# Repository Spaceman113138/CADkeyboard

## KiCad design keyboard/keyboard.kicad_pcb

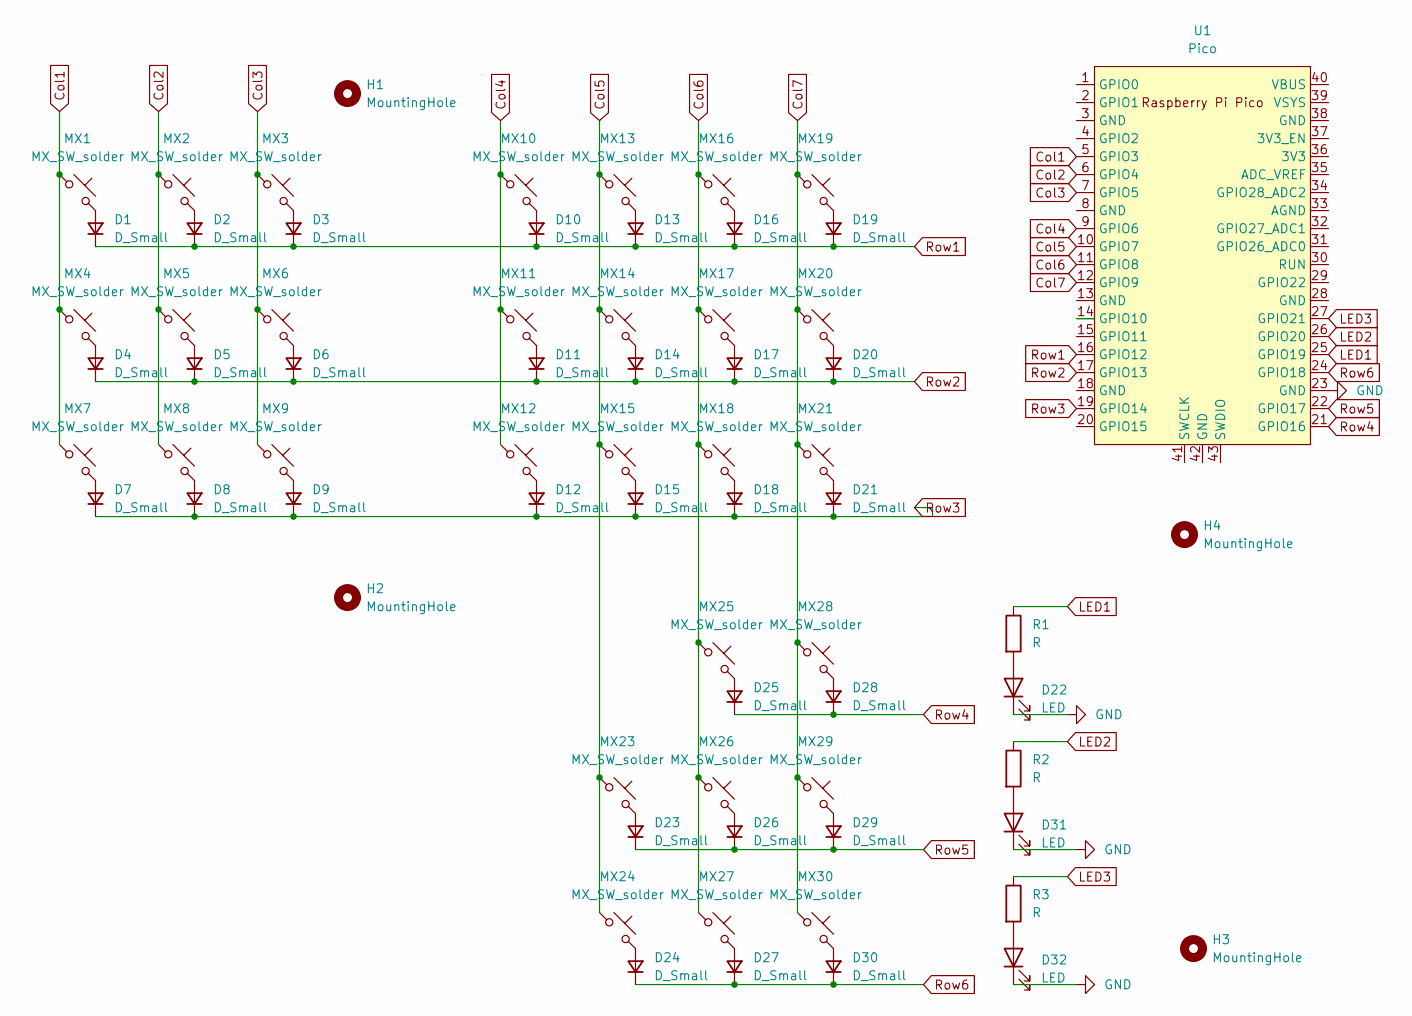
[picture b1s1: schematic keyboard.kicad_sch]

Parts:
D1, D2, D3, D4, D5, D6, D7, D8, D9, D10, D11, D12, D13, D14, D15, D16, D17, D18, D19, D20, D21, D23, D24, D25, D26, D27, D28, D29, D30: D_Small; D_T-1_P5.08mm_Horizontal
D22, D31, D32: LED; LED_D3.0mm
H1, H2, H3, H4: MountingHole; MountingHole_3.2mm_M3_Pad_Via
MX1, MX2, MX3, MX4, MX5, MX6, MX7, MX8, MX9, MX10, MX11, MX12, MX13, MX14, MX15, MX16, MX17, MX18, MX19, MX20, MX21, MX23, MX24, MX25, MX26, MX27, MX28, MX29, MX30: MX_SW_solder; SW_MX_1u
R1, R2, R3: R; R_Axial_DIN0204_L3.6mm_D1.6mm_P5.08mm_Horizontal
U1: Pico; RPi_Pico_SMD_TH

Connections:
Col1: MX1.1, MX4.1, MX7.1, U1.5 (GPIO3)
Col2: MX2.1, MX5.1, MX8.1, U1.6 (GPIO4)
Col3: MX3.1, MX6.1, MX9.1, U1.7 (GPIO5)
Col4: MX10.1, MX11.1, MX12.1, U1.9 (GPIO6)
Col5: MX13.1, MX14.1, MX15.1, MX23.1, MX24.1, U1.10 (GPIO7)
Col6: MX16.1, MX17.1, MX18.1, MX25.1, MX26.1, MX27.1, U1.11 (GPIO8)
Col7: MX19.1, MX20.1, MX21.1, MX28.1, MX29.1, MX30.1, U1.12 (GPIO9)
GND: D22.1 (K), D31.1 (K), D32.1 (K), U1.23 (GND)
LED1: R1.1, U1.25 (GPIO19)
LED2: R2.1, U1.26 (GPIO20)
LED3: R3.1, U1.27 (GPIO21)
unnamed: D1.2 (A), MX1.2
unnamed: D2.2 (A), MX2.2
unnamed: D3.2 (A), MX3.2
unnamed: D4.2 (A), MX4.2
unnamed: D5.2 (A), MX5.2
unnamed: D6.2 (A), MX6.2
unnamed: D7.2 (A), MX7.2
unnamed: D8.2 (A), MX8.2
unnamed: D9.2 (A), MX9.2
unnamed: D10.2 (A), MX10.2
unnamed: D11.2 (A), MX11.2
unnamed: D12.2 (A), MX12.2
unnamed: D13.2 (A), MX13.2
unnamed: D14.2 (A), MX14.2
unnamed: D15.2 (A), MX15.2
unnamed: D16.2 (A), MX16.2
unnamed: D17.2 (A), MX17.2
unnamed: D18.2 (A), MX18.2
unnamed: D19.2 (A), MX19.2
unnamed: D20.2 (A), MX20.2
unnamed: D21.2 (A), MX21.2
unnamed: D22.2 (A), R1.2
unnamed: D23.2 (A), MX23.2
unnamed: D24.2 (A), MX24.2
unnamed: D25.2 (A), MX25.2
unnamed: D26.2 (A), MX26.2
unnamed: D27.2 (A), MX27.2
unnamed: D28.2 (A), MX28.2
unnamed: D29.2 (A), MX29.2
unnamed: D30.2 (A), MX30.2
unnamed: D31.2 (A), R2.2
unnamed: D32.2 (A), R3.2
Row1: D1.1 (K), D2.1 (K), D3.1 (K), D10.1 (K), D13.1 (K), D16.1 (K), D19.1 (K), U1.16 (GPIO12)
Row2: D4.1 (K), D5.1 (K), D6.1 (K), D11.1 (K), D14.1 (K), D17.1 (K), D20.1 (K), U1.17 (GPIO13)
Row3: D7.1 (K), D8.1 (K), D9.1 (K), D12.1 (K), D15.1 (K), D18.1 (K), D21.1 (K), U1.19 (GPIO14)
Row4: D25.1 (K), D28.1 (K), U1.21 (GPIO16)
Row5: D23.1 (K), D26.1 (K), D29.1 (K), U1.22 (GPIO17)
Row6: D24.1 (K), D27.1 (K), D30.1 (K), U1.24 (GPIO18)

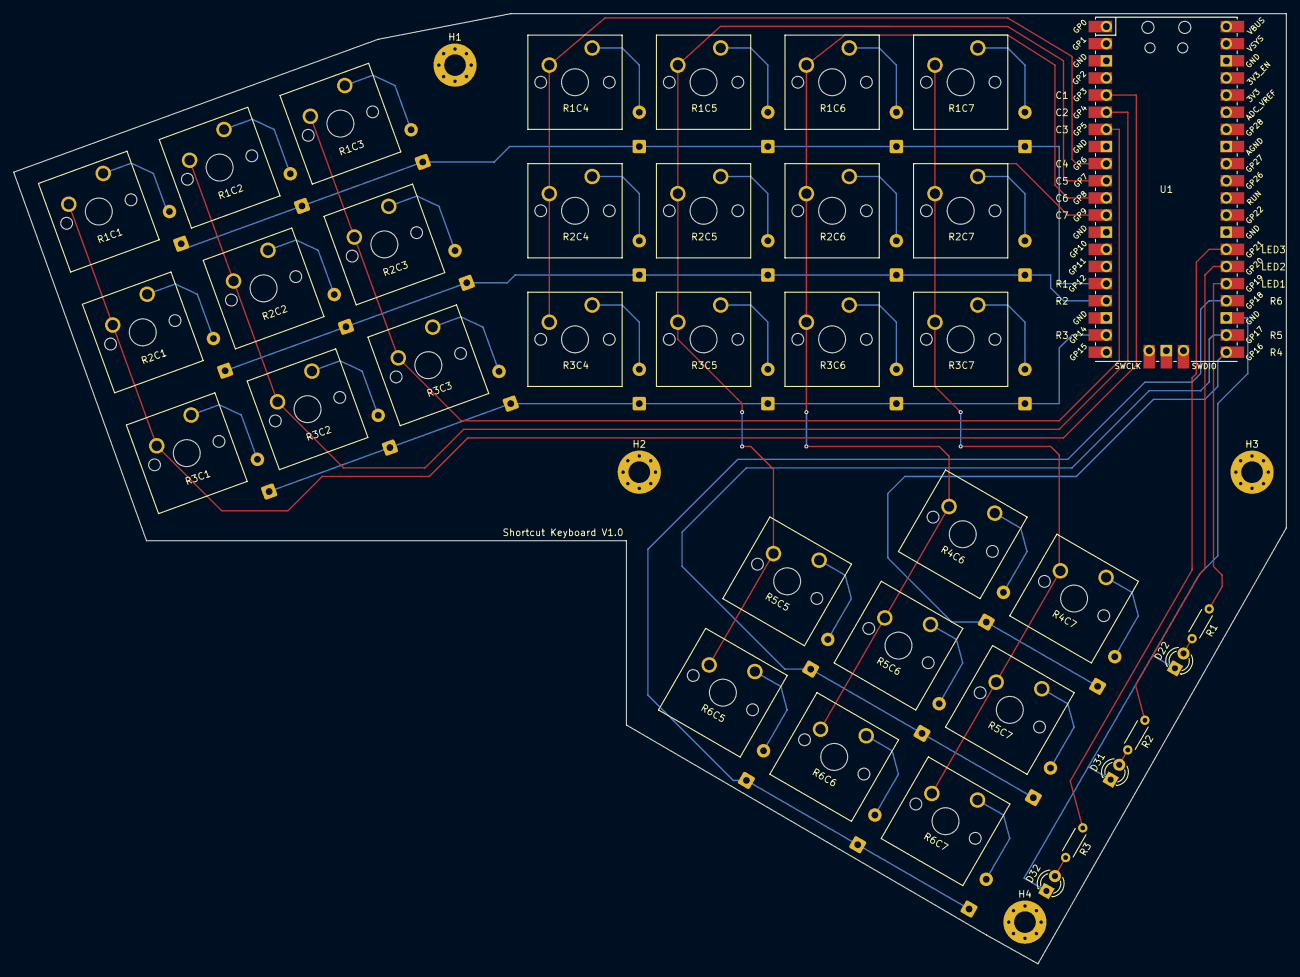
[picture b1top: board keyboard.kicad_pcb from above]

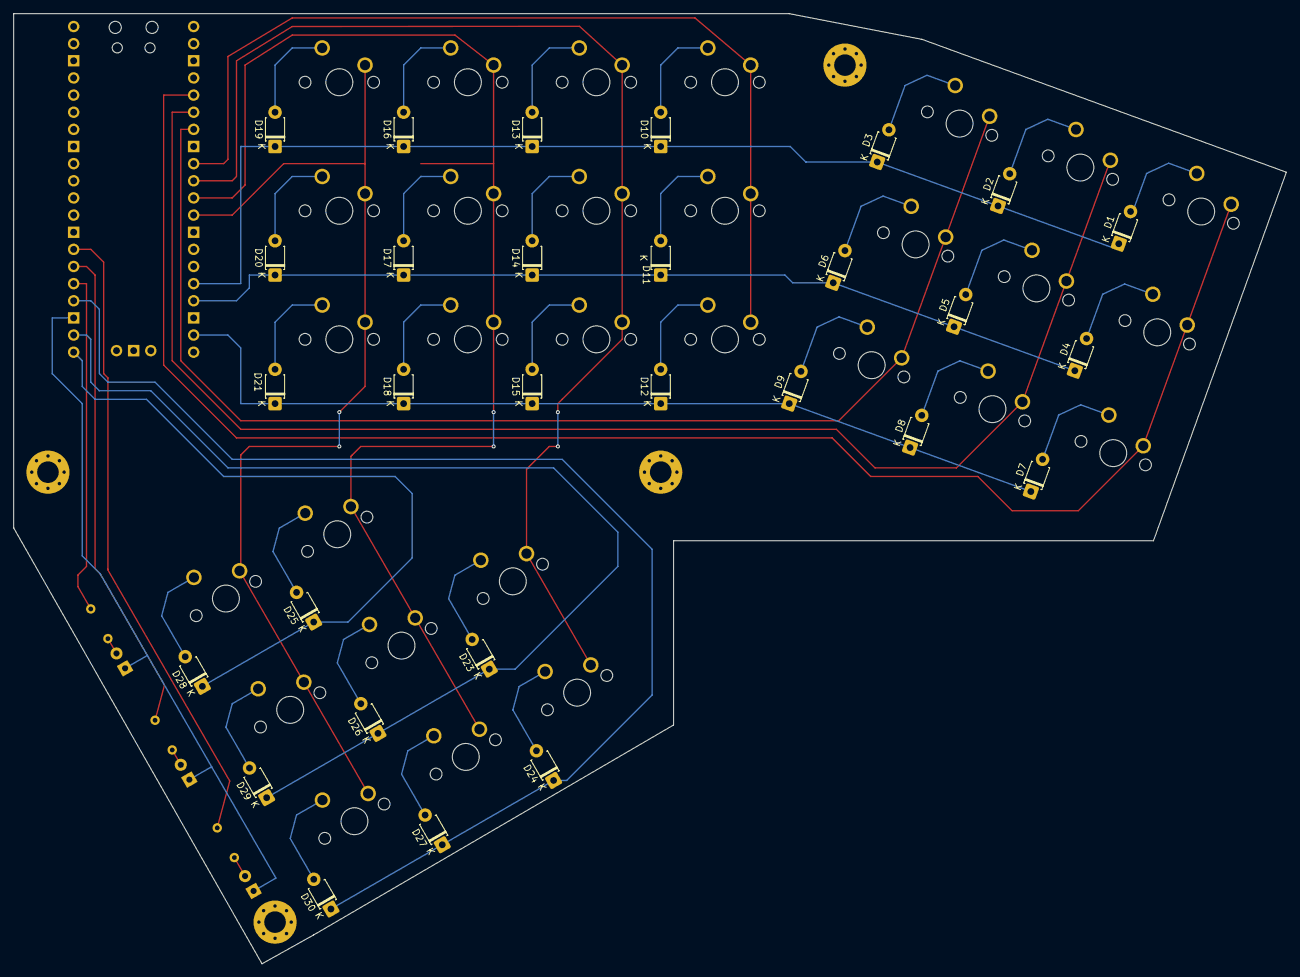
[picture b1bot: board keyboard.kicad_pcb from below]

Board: 2 copper layers, 188.6 x 140.8 mm, 69 parts (29 on the bottom side), 49 nets.

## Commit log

2025-05-25 May 24 journal
2025-05-27 may 26
2025-05-30 May 29
2025-06-05 June 4
2025-06-06 June 5
2025-06-10 pcb files
2025-06-14 writing
